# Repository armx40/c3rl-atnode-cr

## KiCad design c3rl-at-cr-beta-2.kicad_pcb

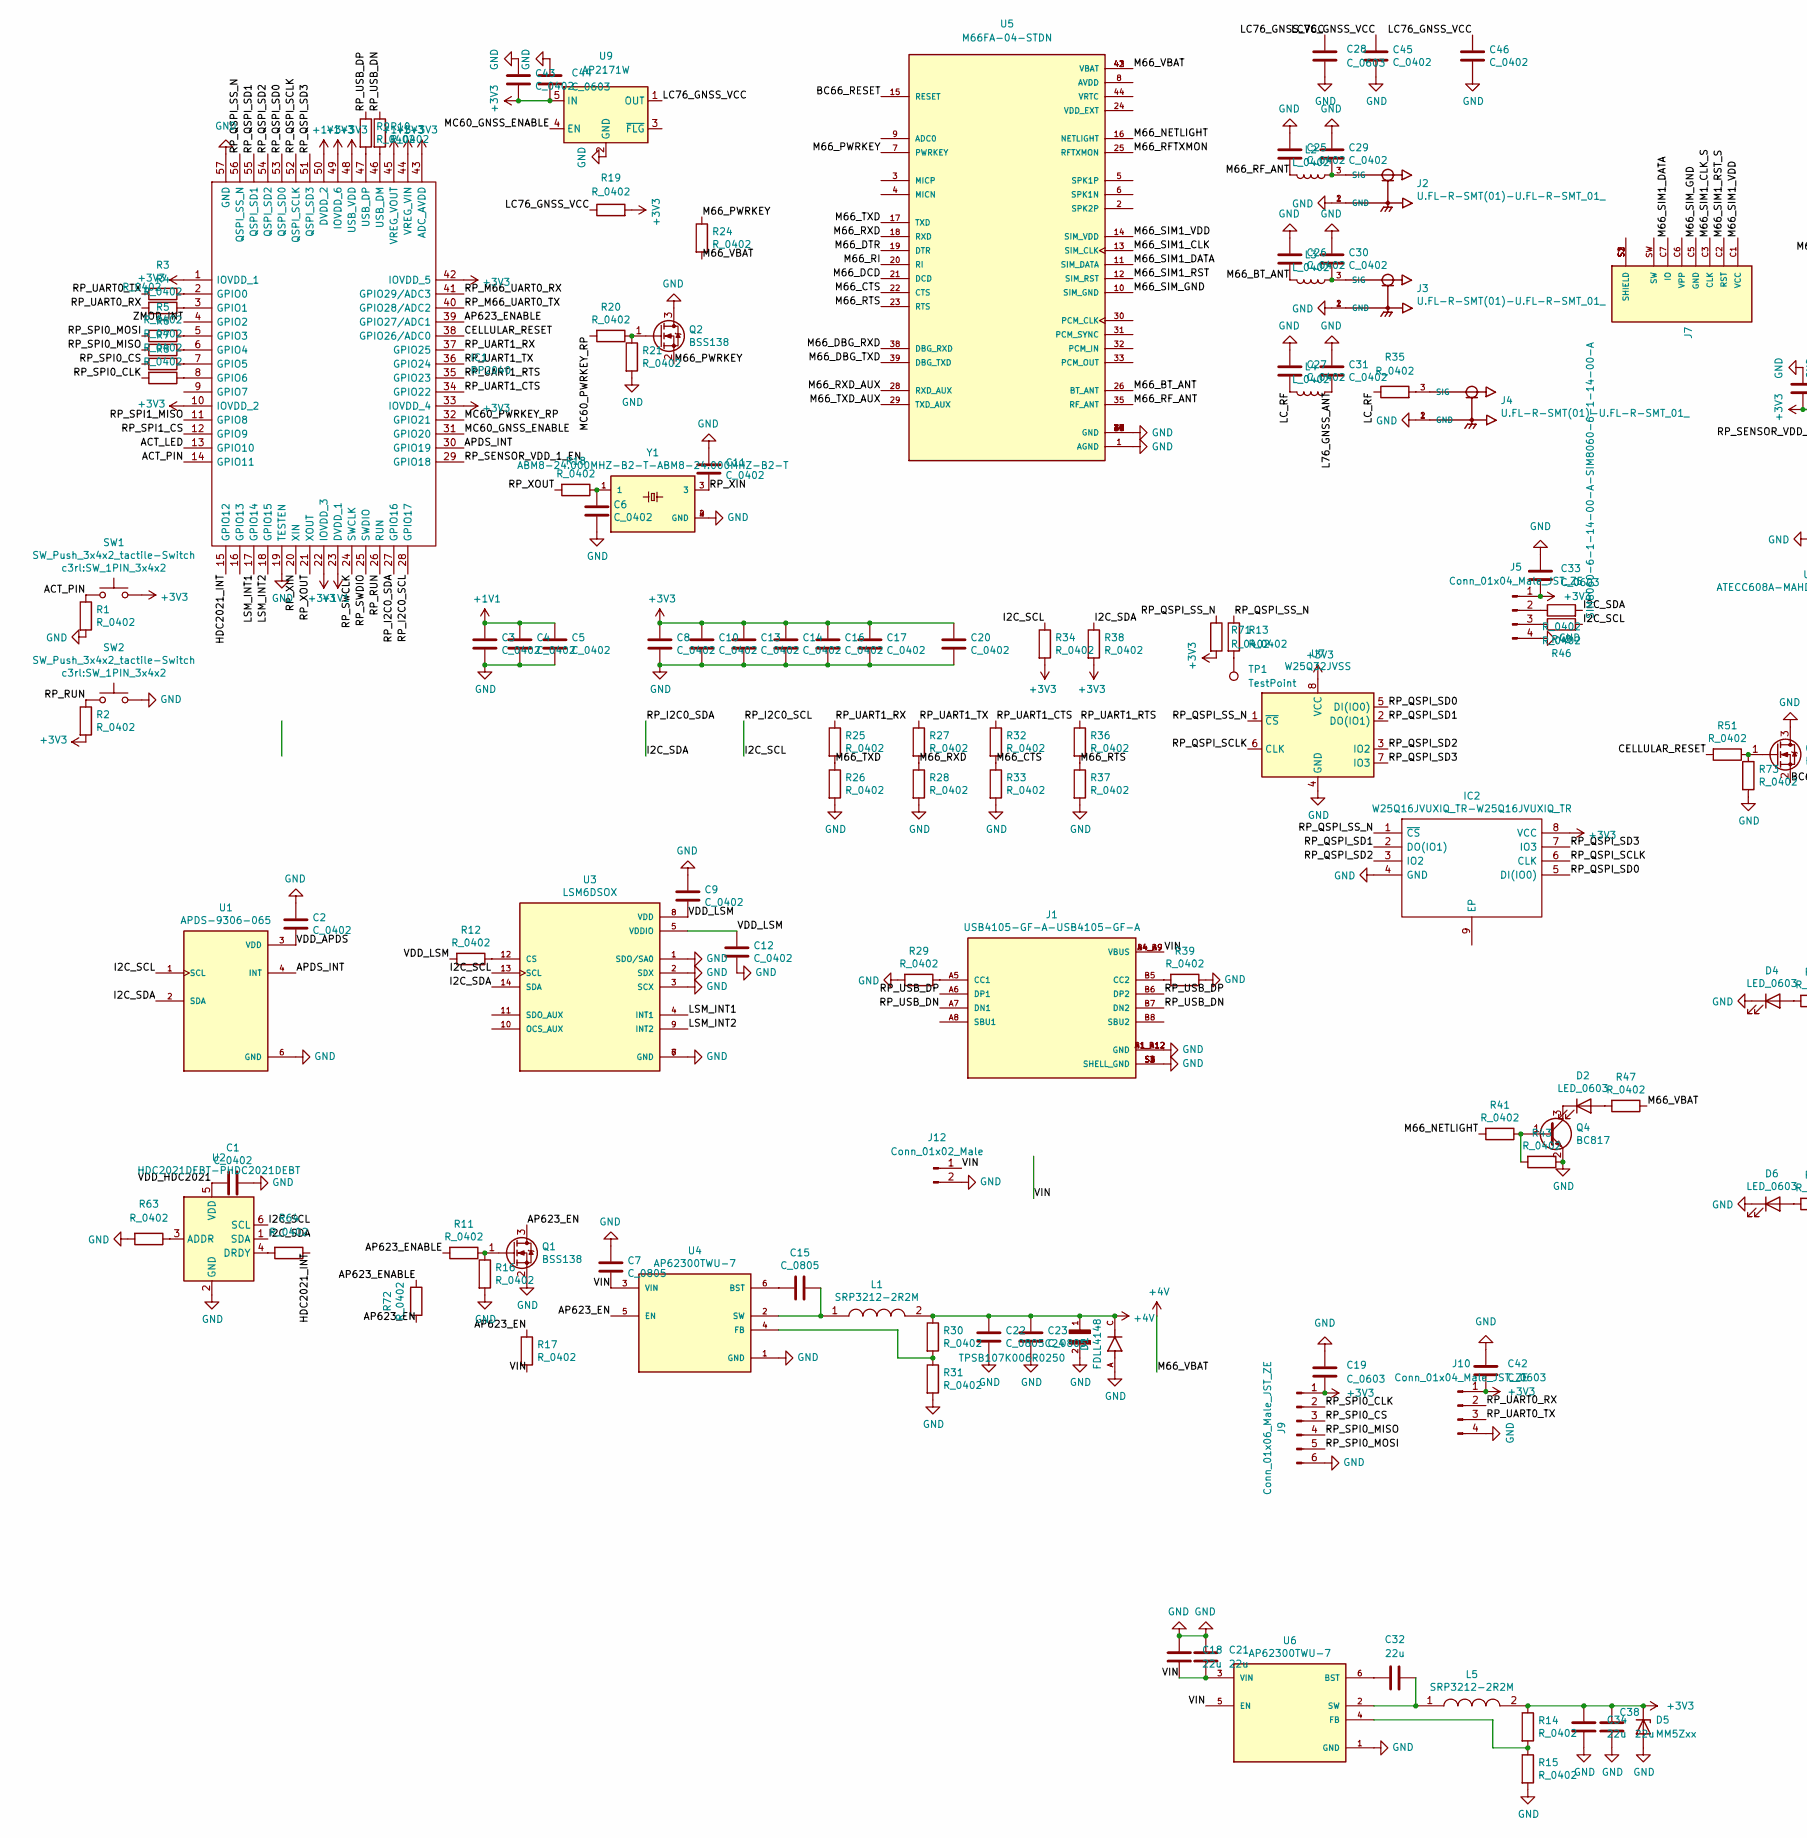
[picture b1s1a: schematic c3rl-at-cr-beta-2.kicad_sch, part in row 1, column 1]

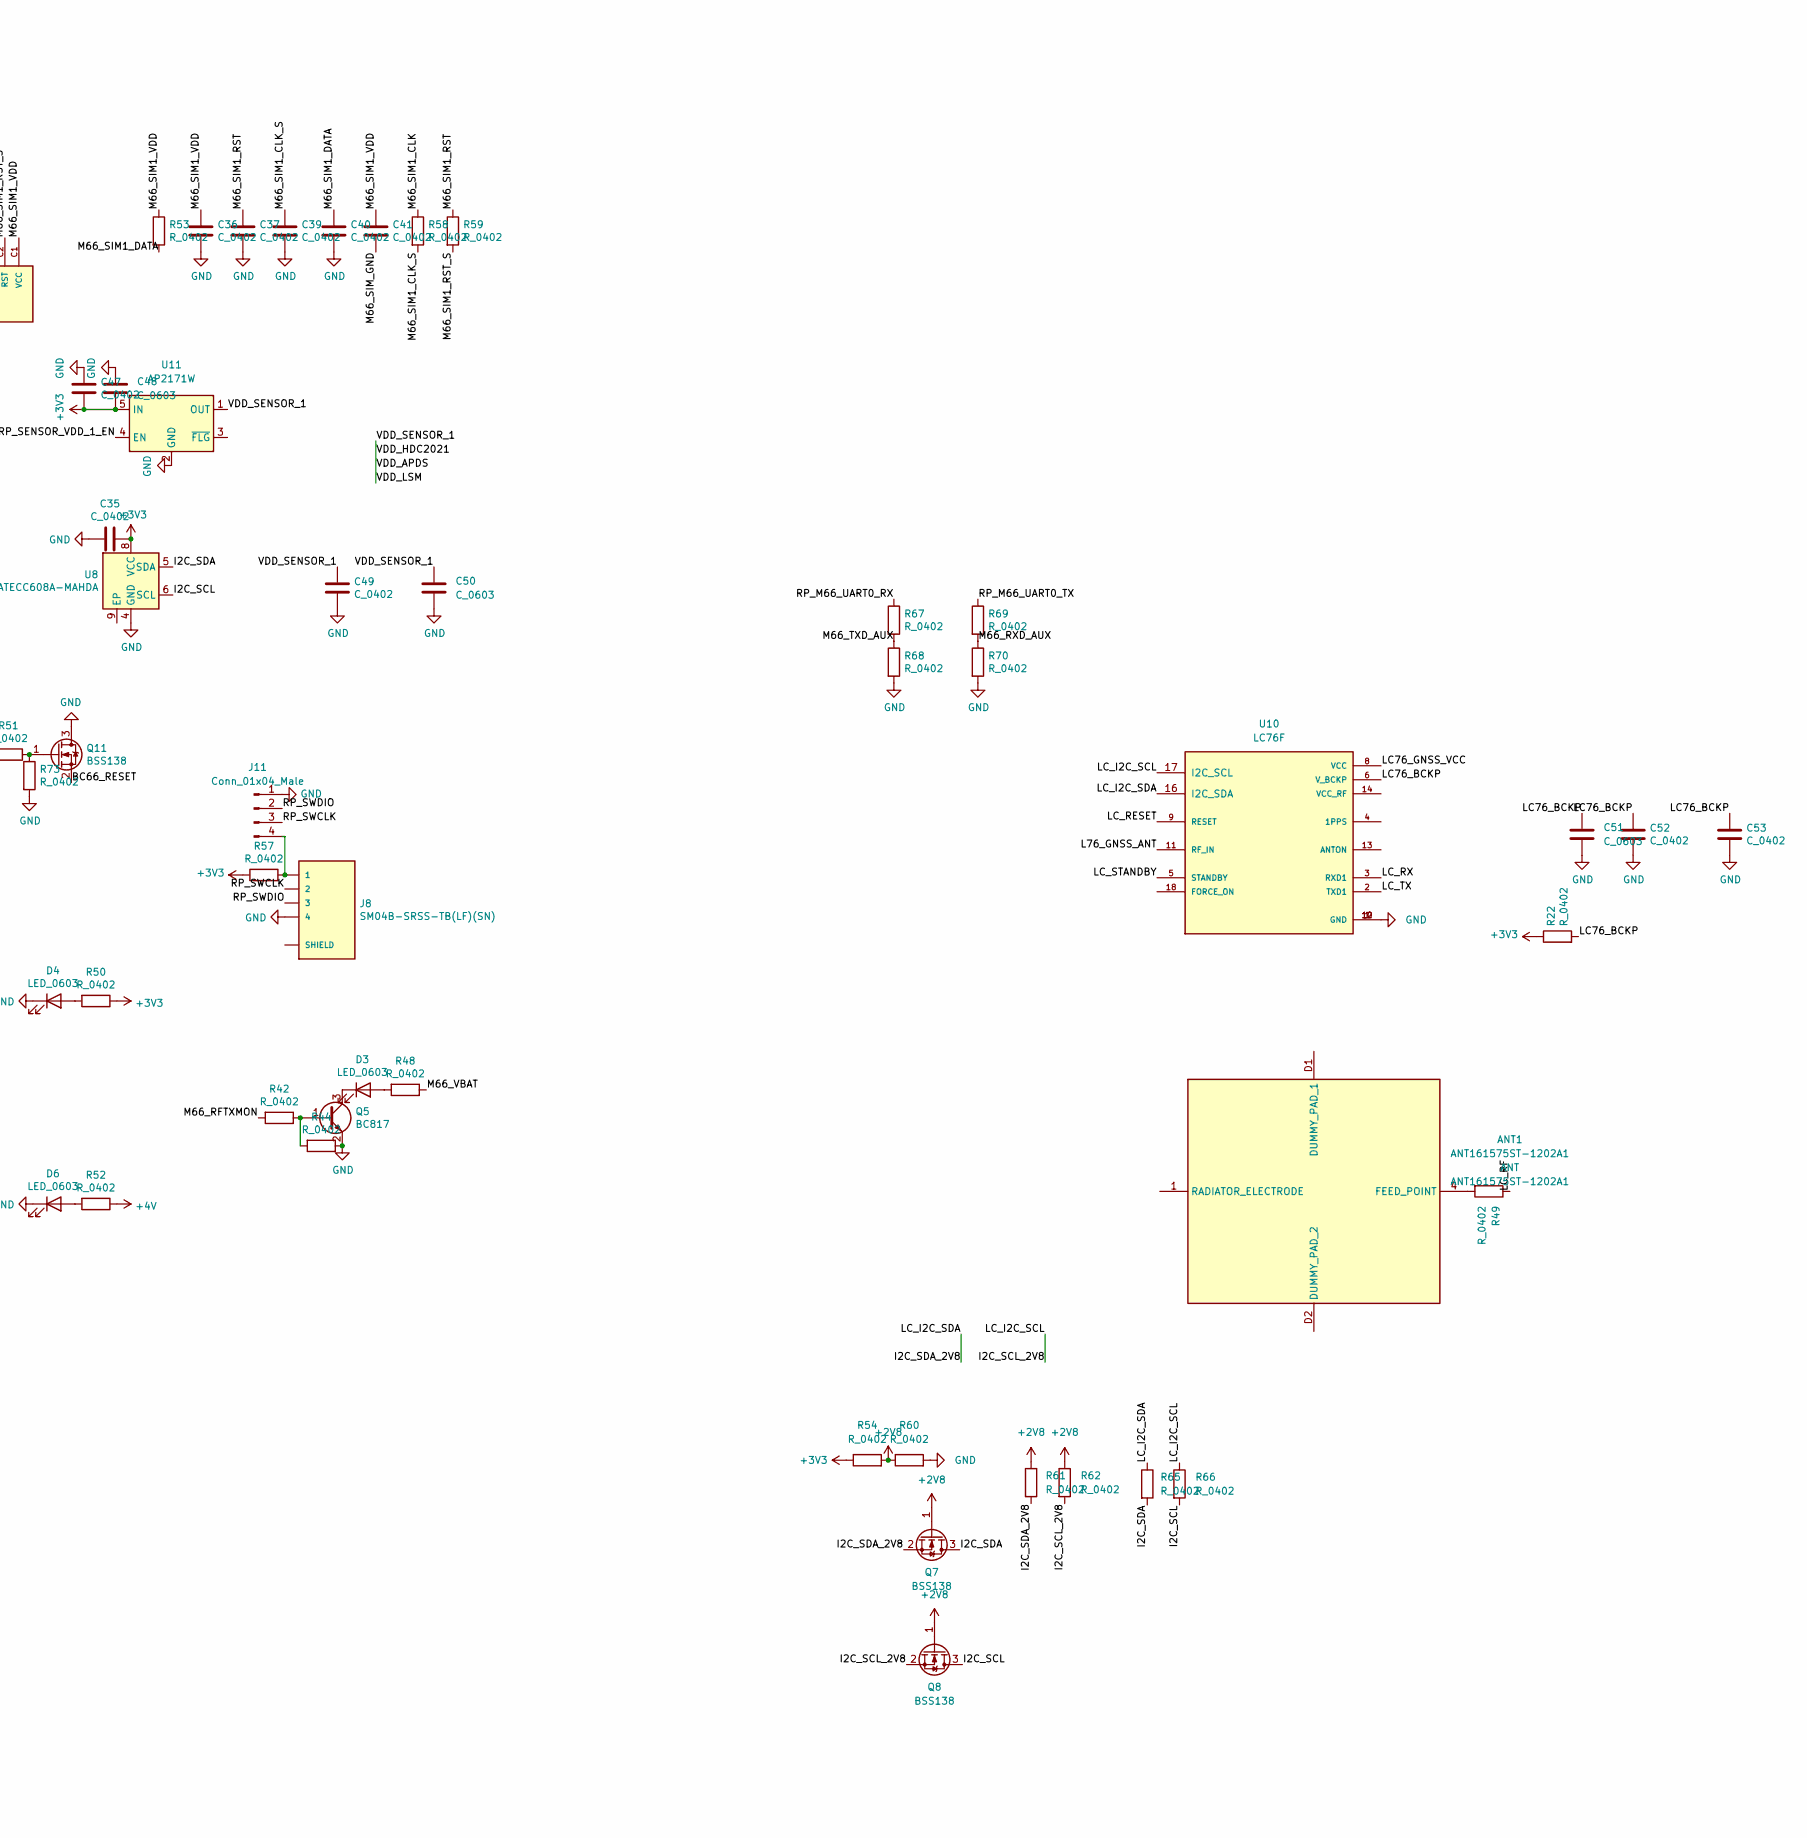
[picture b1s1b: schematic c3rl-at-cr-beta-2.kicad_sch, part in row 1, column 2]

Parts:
ANT1: ANT161575ST-1202A1; ANT161575ST1202A1; Manufacturer_Part_Number ANT161575ST-1202A1; Mouser Part Number 810-ANT161575ST1202A
C1, C2, C3, C4, C5, C6, C8, C9, C10, C11, C12, C13, C14, C16, C17, C20, C25, C26, C27, C29, C30, C31, C35, C36, C37, C39, C40, C41, C43, C45, C46, C47, C49, C52, C53: C_0402; C_0402_1005Metric
C7, C15, C22, C23: C_0805; C_0805_2012Metric
C18, C21, C32, C34, C38: 22u; C_0603_1608Metric
C19, C28, C33, C42, C44, C48, C50, C51: C_0603; C_0603_1608Metric
C24: TPSB107K006R0250; CAPPC3528X210N
D1: FDLL4148; DIOMELF3414N; PARTREV 4
D2, D3, D4, D6: LED_0603; LED_0603_1608Metric
D5: MM5Zxx; D_SOD-523
IC1: RP2040; QFN40P700X700X90-57N-D; Manufacturer_Part_Number RP2040
IC2: W25Q16JVUXIQ_TR-W25Q16JVUXIQ_TR; SON50P300X200X60-9N; Manufacturer_Part_Number W25Q16JVUXIQ TR; Mouser Part Number 454-W25Q16JVUXIQTR
J1: USB4105-GF-A-USB4105-GF-A; GCT_USB4105-GF-A; PARTREV A3
J2, J3, J4: U.FL-R-SMT(01)-U.FL-R-SMT_01_; HRS_U.FL-R-SMT(01)
J5, J10: Conn_01x04_Male_JST_ZE; JST_ZE_B04B-ZESK-D_1x04_P1.50mm_Vertical
J7: SIM8060-6-1-14-00-A-SIM8060-6-1-14-00-A; GCT_SIM8060-6-1-14-00-A; PARTREV A
J8: SM04B-SRSS-TB(LF)(SN); JST_SM04B-SRSS-TB(LF)(SN)
J9: Conn_01x06_Male_JST_ZE; JST_ZE_B06B-ZESK-D_1x06_P1.50mm_Vertical
J11: Conn_01x04_Male; PinHeader_1x04_P1.27mm_Vertical
J12: Conn_01x02_Male; JST_XH_B2B-XH-AM_1x02_P2.50mm_Vertical
L1, L5: SRP3212-2R2M; INDC2520X100N; Manufacturer_Part_Number SRP3212-2R2M
L2, L3, L4: L_0402; L_0402_1005Metric
Q1, Q2, Q7, Q8, Q11: BSS138; SOT-23
Q4, Q5: BC817; SOT-23
R1, R2, R3, R4, R5, R6, R7, R8, R9, R10, R11, R12, R13, R14, R15, R16, R17, R18, R19, R20, R21, R22, R24, R25, R26, R27, R28, R29, R30, R31, R32, R33, R34, R35, R36, R37, R38, R39, R41, R42, R43, R44, R45, R46, R47, R48, R49, R50, R51, R52, R53, R54, R57, R58, R59, R60, R61, R62, R63, R64, R65, R66, R67, R68, R69, R70, R71, R72, R73: R_0402; R_0402_1005Metric
SW1, SW2: SW_Push_3x4x2_tactile-Switch; SW_1PIN_3x4x2
TP1: TestPoint; TestPoint_Pad_1.0x1.0mm
U1: APDS-9306-065; SON65P200X200X75-6N
U2: HDC2021DEBT-PHDC2021DEBT; PHDC2021DEBT
U3: LSM6DSOX; PQFN50P250X300X86-14N; PARTREV 3.0
U4, U6: AP62300TWU-7; SOT95P280X100-6N; PARTREV Rev. 3 - 2
U5: M66FA-04-STDN; XCVR_M66FA-04-STDN
U7: W25Q32JVSS; SOIC-8_5.23x5.23mm_P1.27mm
U8: ATECC608A-MAHDA; DFN-8-1EP_3x2mm_P0.5mm_EP1.3x1.5mm
U9, U11: AP2171W; SOT-23-5
U10: LC76F; XCVR_L76LBA31
Y1: ABM8-24.000MHZ-B2-T-ABM8-24.000MHZ-B2-T; OSCSC320X250X100N

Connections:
+1V1: C3.1, C4.1, C5.1, IC1.23 (DVDD_1), IC1.45 (VREG_VOUT), IC1.50 (DVDD_2)
+2V8: Q7.1 (G), Q8.1 (G), R54.2, R60.1, R61.1, R62.1
+3V3: C8.1, C10.1, C13.1, C14.1, C16.1, C17.1, C19.2, C20.1, C33.2, C34.1, C35.2, C38.1, C42.2, C43.1, C44.2, C47.1, C48.2, D5.1 (K), IC1.1 (IOVDD_1), IC1.10 (IOVDD_2), IC1.22 (IOVDD_3), IC1.33 (IOVDD_4), IC1.42 (IOVDD_5), IC1.43 (ADC_AVDD), IC1.44 (VREG_VIN), IC1.48 (USB_VDD), IC1.49 (IOVDD_6), IC2.8 (VCC), J5.1, J9.1, J10.1, L5.2, R2.2, R14.1, R19.2, R22.1, R34.2, R38.2, R50.1, R54.1, R57.1, R71.2, SW1.2, U7.8 (VCC), U8.8 (VCC), U9.5 (IN), U11.5 (IN)
+4V: C22.1, C23.1, C24.1, D1.C, L1.2, R24.2, R30.1, R47.1, R48.1, R52.1, U5.42 (VBAT), U5.43 (VBAT)
/ACT_LED: IC1.13 (GPIO10)
/ACT_PIN: IC1.14 (GPIO11), R1.1, SW1.1
/AP623_EN: Q1.3 (D), R17.1, R72.2, U4.5 (EN)
/AP623_ENABLE: IC1.39 (GPIO27/ADC1), R11.2, R72.1
/APDS_INT: IC1.30 (GPIO19), U1.4 (INT)
/BC66_RESET: Q11.2 (S), U5.15 (RESET)
/CELLULAR_RESET: IC1.38 (GPIO26/ADC0), R51.2
/HDC2021_INT: IC1.15 (GPIO12), R64.1
/I2C_SCL: IC1.28 (GPIO17), Q8.3 (D), R34.1, R46.2, R66.2, U1.1 (SCL), U2.6 (SCL), U3.13 (SCL), U8.6 (SCL)
/I2C_SCL_2V8: Q8.2 (S), R62.2, R66.1, U10.17 (I2C_SCL)
/I2C_SDA: IC1.27 (GPIO16), Q7.3 (D), R38.1, R45.2, R65.2, U1.2 (SDA), U2.1 (SDA), U3.14 (SDA), U8.5 (SDA)
/I2C_SDA_2V8: Q7.2 (S), R61.2, R65.1, U10.16 (I2C_SDA)
/L76_GNSS_ANT: C31.2, L4.1, U10.11 (RF_IN)
/LC76_BCKP: C51.1, C52.2, C53.2, R22.2, U10.6 (V_BCKP)
/LC76_GNSS_VCC: C28.1, C45.2, C46.2, R19.1, U9.1 (OUT), U10.8 (VCC)
/LC_RESET: U10.9 (RESET)
/LC_RF: C27.2, L4.2, R35.1, R49.1
/LC_RX: U10.3 (RXD1)
/LC_STANDBY: U10.5 (STANDBY)
/LC_TX: U10.2 (TXD1)
/LSM_INT1: IC1.17 (GPIO14), U3.4 (INT1)
/LSM_INT2: IC1.18 (GPIO15), U3.9 (INT2)
/M66_BT_ANT: C26.2, L3.2, U5.26 (BT_ANT)
/M66_CTS: R32.2, R33.1, U5.22 (CTS)
/M66_DBG_RXD: U5.38 (DBG_RXD)
/M66_DBG_TXD: U5.39 (DBG_TXD)
/M66_DCD: U5.21 (DCD)
/M66_DTR: U5.19 (DTR)
/M66_NETLIGHT: R41.2, U5.16 (NETLIGHT)
/M66_PWRKEY: Q2.2 (S), R24.1, U5.7 (PWRKEY)
/M66_RFTXMON: R42.2, U5.25 (RFTXMON)
/M66_RF_ANT: C25.1, L2.2, U5.35 (RF_ANT)
/M66_RI: U5.20 (RI)
/M66_RTS: R36.2, R37.1, U5.23 (RTS)
/M66_RXD: R27.2, R28.1, U5.18 (RXD)
/M66_RXD_AUX: R69.2, R70.1, U5.28 (RXD_AUX)
/M66_SIM1_CLK: R58.1, U5.13 (SIM_CLK)
/M66_SIM1_CLK_S: C39.1, J7.C3 (CLK), R58.2
/M66_SIM1_DATA: C40.1, J7.C7 (IO), R53.2, U5.11 (SIM_DATA)
/M66_SIM1_RST: C37.1, R59.1, U5.12 (SIM_RST)
/M66_SIM1_RST_S: J7.C2 (RST), R59.2
/M66_SIM1_VDD: C36.1, C41.1, J7.C1 (VCC), R53.1, U5.14 (SIM_VDD)
/M66_SIM_GND: C41.2, J7.C5 (GND), U5.10 (SIM_GND)
/M66_TXD: R25.2, R26.1, U5.17 (TXD)
/M66_TXD_AUX: R67.2, R68.1, U5.29 (TXD_AUX)
/MC60_GNSS_ENABLE: IC1.31 (GPIO20), U9.4 (EN)
/MC60_PWRKEY_RP: IC1.32 (GPIO21), R20.2
/RP_M66_UART0_RX: IC1.41 (GPIO29/ADC3), R67.1
/RP_M66_UART0_TX: IC1.40 (GPIO28/ADC2), R69.1
/RP_QSPI_SCLK: IC1.52 (QSPI_SCLK), IC2.6 (CLK), U7.6 (CLK)
/RP_QSPI_SD0: IC1.53 (QSPI_SD0), IC2.5 (DI(IO0)), U7.5 (DI(IO0))
/RP_QSPI_SD1: IC1.55 (QSPI_SD1), IC2.2 (DO(IO1)), U7.2 (DO(IO1))
/RP_QSPI_SD2: IC1.54 (QSPI_SD2), IC2.3 (IO2), U7.3 (IO2)
/RP_QSPI_SD3: IC1.51 (QSPI_SD3), IC2.7 (IO3), U7.7 (IO3)
/RP_QSPI_SS_N: IC1.56 (QSPI_SS_N), IC2.1 (~CS), R13.1, R71.1, U7.1 (~CS)
/RP_RUN: IC1.26 (RUN), R2.1, SW2.1
/RP_SENSOR_VDD_1_EN: IC1.29 (GPIO18), U11.4 (EN)
/RP_SPI0_CLK: J9.2, R8.2
/RP_SPI0_CS: J9.3, R7.2
/RP_SPI0_MISO: J9.4, R6.2
/RP_SPI0_MOSI: J9.5, R5.2
/RP_SPI1_CS: IC1.12 (GPIO9)
/RP_SPI1_MISO: IC1.11 (GPIO8)
/RP_SWCLK: IC1.24 (SWCLK), J8.2, J11.3
/RP_SWDIO: IC1.25 (SWDIO), J8.3, J11.2
/RP_UART0_RX: J10.2, R4.2
/RP_UART0_TX: J10.3, R3.2
/RP_UART1_CTS: IC1.34 (GPIO22), R32.1
/RP_UART1_RTS: IC1.35 (GPIO23), R36.1
/RP_UART1_RX: IC1.37 (GPIO25), R25.1
/RP_UART1_TX: IC1.36 (GPIO24), R27.1
/RP_USB_DN: J1.A7 (DN1), J1.B7 (DN2), R10.1
/RP_USB_DP: J1.A6 (DP1), J1.B6 (DP2), R9.1
/RP_XIN: C11.2, IC1.20 (XIN), Y1.3
/RP_XOUT: IC1.21 (XOUT), R18.2
/VDD_APDS: C1.2, C2.2, C9.2, C12.1, C49.2, C50.1, R12.2, U1.3 (VDD), U2.5 (VDD), U3.5 (VDDIO), U3.8 (VDD), U11.1 (OUT)
/VIN: C7.2, C18.2, C21.2, J1.A4_B9 (VBUS), J1.B4_A9 (VBUS), J12.1, R17.2, U4.3 (VIN), U6.3 (VIN), U6.5 (EN)
/ZMOD_INT: IC1.4 (GPIO2)
GND: C1.1, C2.1, C3.2, C4.2, C5.2, C6.1, C7.1, C8.2, C9.1, C10.2, C11.1, C12.2, C13.2, C14.2, C16.2, C17.2, C18.1, C19.1, C20.2, C21.1, C22.2, C23.2, C24.2, C25.2, C26.1, C27.1, C28.2, C29.1, C30.1, C31.1, C33.1, C34.2, C35.1, C36.2, C37.2, C38.2, C39.2, C40.2, C42.1, C43.2, C44.1, C45.1, C46.1, C47.2, C48.1, C49.1, C50.2, C51.2, C52.1, C53.1, D1.A, D4.1 (K), D5.2 (A), D6.1 (K), IC1.19 (TESTEN), IC1.57 (GND), IC2.4 (GND), J1.A1_B12 (GND), J1.B1_A12 (GND), J1.S1 (SHELL_GND), J1.S2 (SHELL_GND), J1.S3 (SHELL_GND), J1.S4 (SHELL_GND), J2.1 (GND), J2.2 (GND), J3.1 (GND), J3.2 (GND), J4.1 (GND), J4.2 (GND), J5.4, J8.4, J9.6, J10.4, J11.1, J12.2, Q1.2 (S), Q2.3 (D), Q4.2 (E), Q5.2 (E), Q11.3 (D), R1.2, R15.2, R16.2, R21.2, R26.2, R28.2, R29.2, R31.2, R33.2, R37.2, R39.1, R43.1, R44.1, R60.2, R63.2, R68.2, R70.2, R73.2, SW2.2, U1.6 (GND), U2.2 (GND), U3.1 (SDO/SA0), U3.2 (SDX), U3.3 (SCX), U3.6 (GND), U3.7 (GND), U4.1 (GND), U5.1 (AGND), U5.27 (GND), U5.34 (GND), U5.36 (GND), U5.37 (GND), U5.40 (GND), U5.41 (GND), U6.1 (GND), U7.4 (GND), U8.4 (GND), U9.2 (GND), U10.1 (GND), U10.10 (GND), U10.12 (GND), U11.2 (GND), Y1.2 (GND), Y1.4 (GND)
unnamed: ANT1.4 (FEED_POINT), R49.2
unnamed: C6.2, R18.1, Y1.1
unnamed: C15.1, L1.1, U4.2 (SW)
unnamed: C15.2, U4.6 (BST)
unnamed: C29.2, J2.3 (SIG), L2.1
unnamed: C30.2, J3.3 (SIG), L3.1
unnamed: C32.1, U6.6 (BST)
unnamed: C32.2, L5.1, U6.2 (SW)
unnamed: D2.1 (K), Q4.3 (C)
unnamed: D2.2 (A), R47.2
unnamed: D3.1 (K), Q5.3 (C)
unnamed: D3.2 (A), R48.2
unnamed: D4.2 (A), R50.2
unnamed: D6.2 (A), R52.2
unnamed: IC1.2 (GPIO0), R3.1
unnamed: IC1.3 (GPIO1), R4.1
unnamed: IC1.5 (GPIO3), R5.1
unnamed: IC1.6 (GPIO4), R6.1
unnamed: IC1.7 (GPIO5), R7.1
unnamed: IC1.8 (GPIO6), R8.1
unnamed: IC1.46 (USB_DM), R10.2
unnamed: IC1.47 (USB_DP), R9.2
unnamed: J1.A5 (CC1), R29.1
unnamed: J1.B5 (CC2), R39.2
unnamed: J4.3 (SIG), R35.2
unnamed: J5.2, R45.1
unnamed: J5.3, R46.1
unnamed: J7.S1 (SHIELD), J7.S2 (SHIELD), J7.S3 (SHIELD)
unnamed: J8.S1 (SHIELD), J8.S2 (SHIELD)
unnamed: J8.1, J11.4, R57.2
unnamed: Q1.1 (G), R11.1, R16.1
unnamed: Q2.1 (G), R20.1, R21.1
unnamed: Q4.1 (B), R41.1, R43.2
unnamed: Q5.1 (B), R42.1, R44.2
unnamed: Q11.1 (G), R51.1, R73.1
unnamed: R12.1, U3.12 (CS)
unnamed: R13.2, TP1.1
unnamed: R14.2, R15.1, U6.4 (FB)
unnamed: R30.2, R31.1, U4.4 (FB)
unnamed: R63.1, U2.3 (ADDR)
unnamed: R64.2, U2.4 (DRDY)

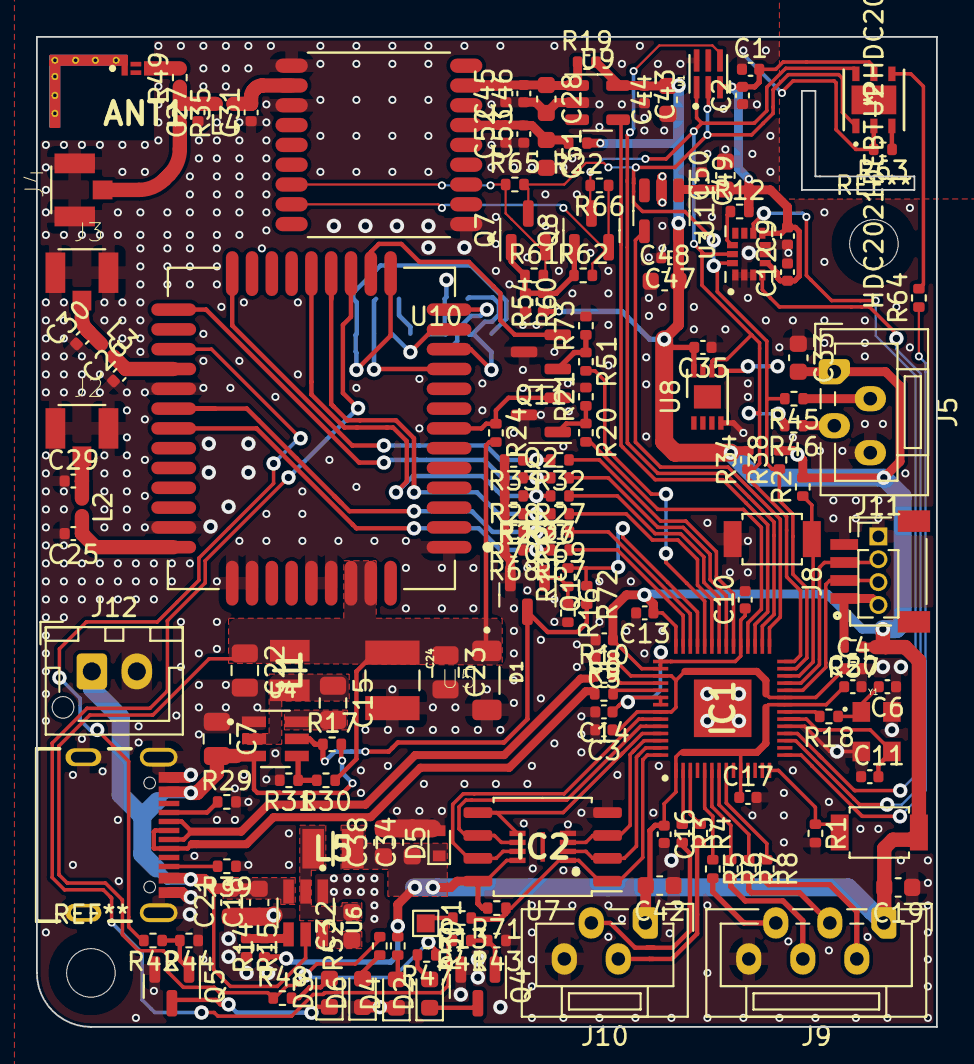
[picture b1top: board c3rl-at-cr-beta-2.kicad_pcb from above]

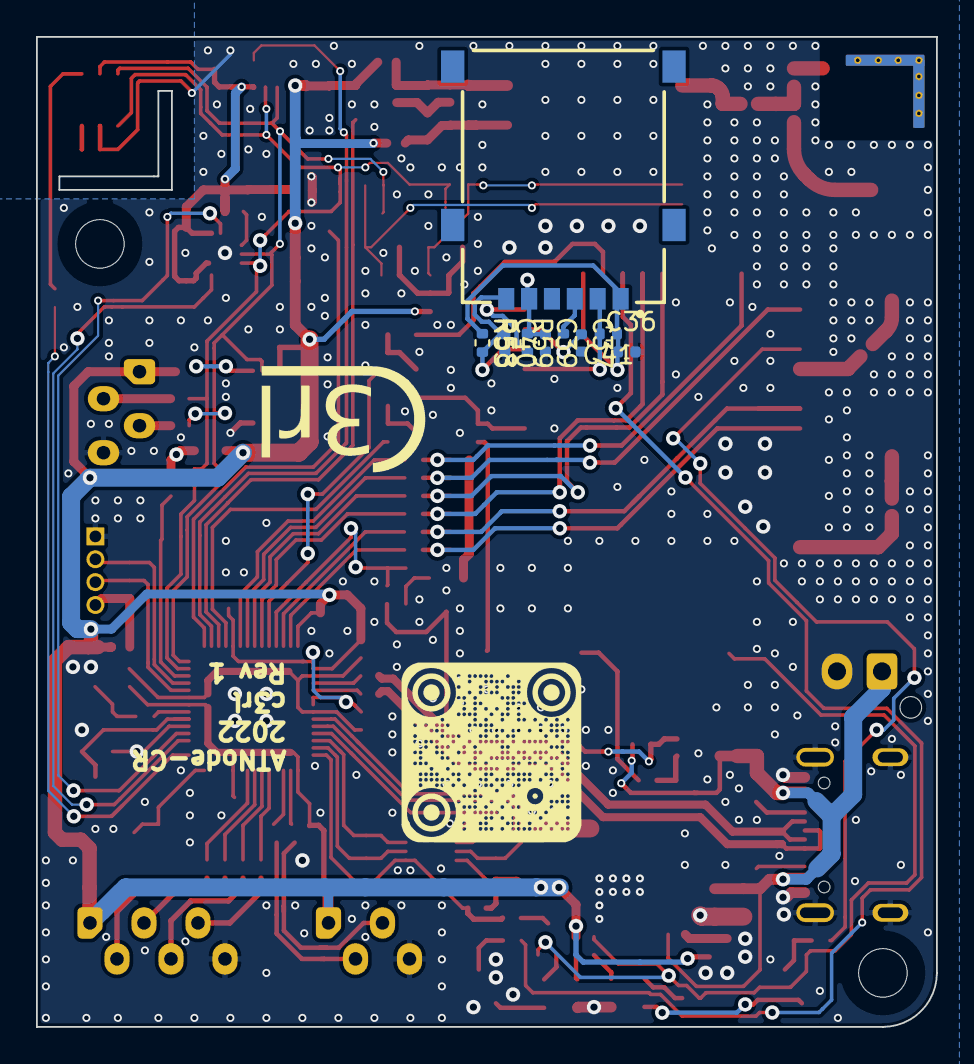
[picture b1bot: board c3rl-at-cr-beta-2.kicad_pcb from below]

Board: 2 copper layers, 50.0 x 55.0 mm, 169 parts (9 on the bottom side), 111 nets.

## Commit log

2023-11-19 rev1

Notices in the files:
parts and their libraries:
Copyright 2016 Accelerated Designs. All rights reserved.
